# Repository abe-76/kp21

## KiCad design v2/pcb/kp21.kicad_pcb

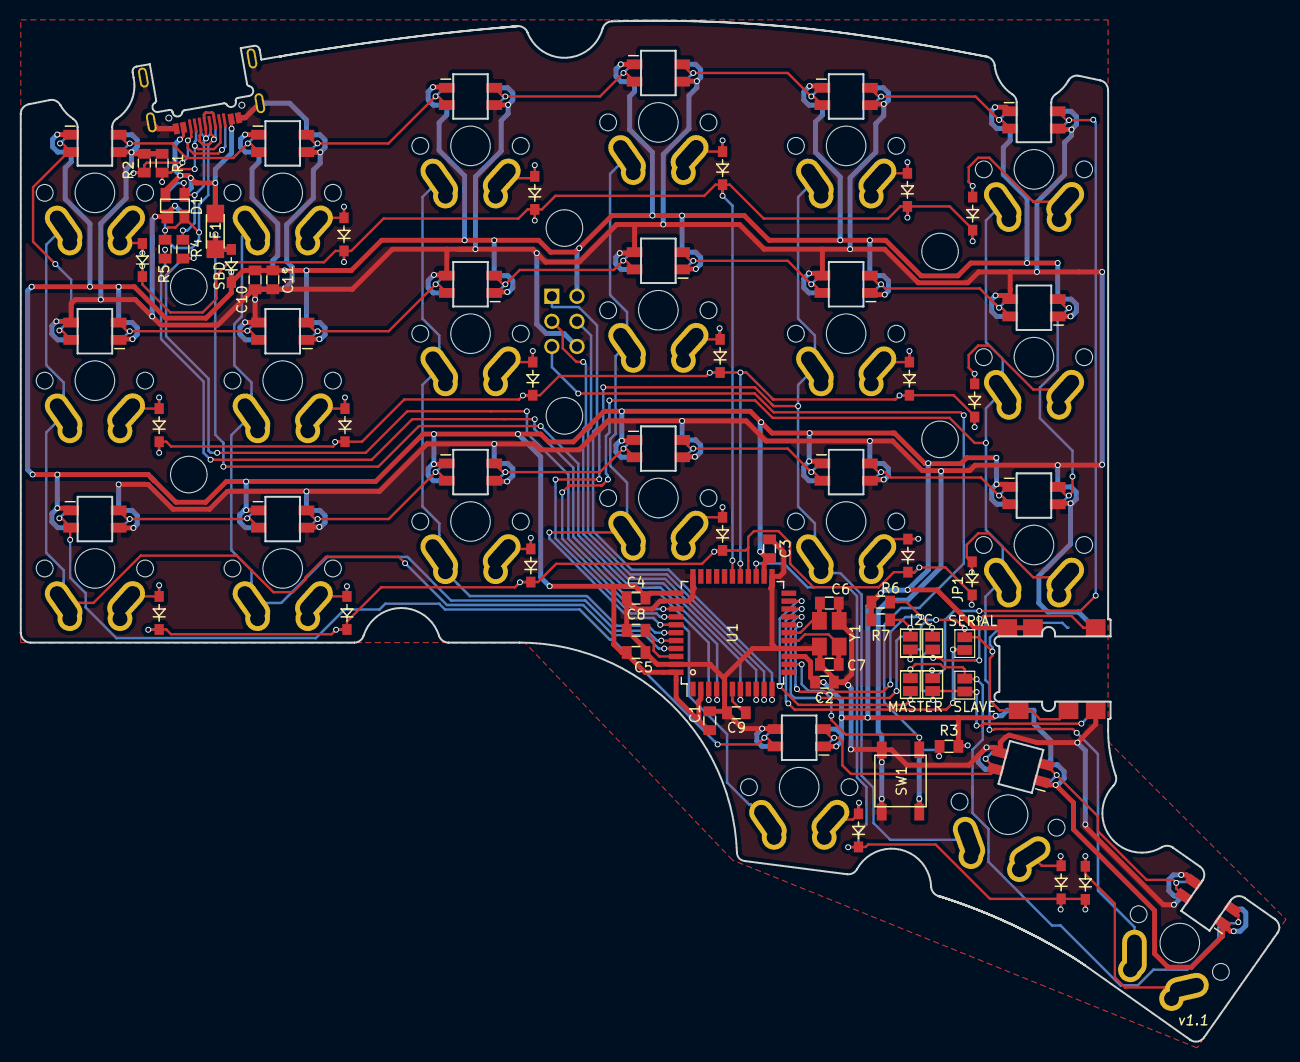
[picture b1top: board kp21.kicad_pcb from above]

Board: 2 copper layers, 127.3 x 103.3 mm, 96 parts (0 on the bottom side), 77 nets.

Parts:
C1, C2, C3, C4, C5, C8: 0.1u; 0805
C6, C7: 22p; 0805
C9: 1u; 0805
C10: 10u; 0805_rev
C11: 0.1u; 0805_rev
D1: PRTR5V0U2X; SOT-143_rev
D2: SBD; SOD-123_rev
D3, D4, D5, D6, D7, D8, D9, D10, D11, D12, D13, D14, D15, D16, D17, D18, D19, D20, D21, D22, D23: D; SOD-123_rev
F1: Polyfuse_Small; 1206_rev
J1: AVR-ISP-6
J2: 3.5mm_sj-43504_smt_tr; sj-43504
JP1, JP2, JP3, JP4, JP5, JP6: Jumper_NO_Small; SolderJumper-2_P1.3mm_Open_Pad1.0x1.5mm_rev
P1: USB_TYPE-C-31-M-14; TYPE_C_31_M_14
R1, R2: 5.1k; 0805_rev
R3: 10k; 0805_rev
R4, R5: 22; 0805_rev
R6, R7: 4.7k; 0805
SW1: SW_Push; Switch_SMD
SW2, SW3, SW4, SW5, SW6, SW7, SW8, SW9, SW10, SW11, SW12, SW13, SW14, SW15, SW16, SW17, SW18, SW19, SW20, SW21, SW22: SW_Push; SW_MX_ALPS_1u
U1: ATmega32U4; TQFP_44_pitch0.8mm
U2, U3, U4, U5, U6, U7, U8, U9, U10, U11, U12, U13, U14, U15, U16, U17, U18, U19, U20, U21, U22: SK6812mini; SK6812MINI_rev
Y1: Crystal_GND24; SMD_3225_4p

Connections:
/LED_IN: JP4.1, JP6.2, U22.3
/RESET: J1.5, R3.2, SW1.2, U1.13
/SCL: JP1.1, R6.2, U1.18
/SDA: JP2.1, R7.2, U1.19
/VBUS: D2.2, F1.1, U1.7
D+: R5.2, U1.4
D-: R4.2, U1.3
EXTRA: JP5.1, U19.1
GND: C1.2, C2.2, C3.2, C4.2, C5.2, C6.2, C7.2, C8.2, C9.2, C10.2, C11.2, D1.1, J1.6, J2.1, P1.1, P1.12, P1.13, R1.2, R2.2, SW1.1, U1.5, U1.15, U1.23, U1.33, U1.35, U1.43, U2.2, U3.2, U4.2, U5.2, U6.2, U7.2, U8.2, U9.2, U10.2, U11.2, U12.2, U13.2, U14.2, U15.2, U16.2, U17.2, U18.2, U19.2, U20.2, U21.2, U22.2, Y1.2, Y1.4
LED: JP6.1, U1.21
MISO: J1.1, U1.11
MOSI: J1.4, U1.10
unnamed: C6.1, U1.17, Y1.1
unnamed: C7.1, U1.16, Y1.3
unnamed: C8.1, U1.42
unnamed: C9.1, U1.6
unnamed: D1.2, P1.6, P1.8, R5.1
unnamed: D1.3, P1.5, P1.7, R4.1
unnamed: D1.4, F1.2, P1.2, P1.11
unnamed: D3.2, SW2.2
unnamed: D4.2, SW3.2
unnamed: D5.2, SW4.2
unnamed: D6.2, SW5.2
unnamed: D7.2, SW6.2
unnamed: D8.2, SW7.2
unnamed: D9.2, SW8.2
unnamed: D10.2, SW9.2
unnamed: D11.2, SW10.2
unnamed: D12.2, SW11.2
unnamed: D13.2, SW12.2
unnamed: D14.2, SW13.2
unnamed: D15.2, SW14.2
unnamed: D16.2, SW15.2
unnamed: D17.2, SW16.2
unnamed: D18.2, SW17.2
unnamed: D19.2, SW18.2
unnamed: D20.2, SW19.2
unnamed: D21.2, SW20.2
unnamed: D22.2, SW21.2
unnamed: D23.2, SW22.2
unnamed: J2.3, J2.6, JP2.2, JP3.2
unnamed: J2.4, JP1.2, JP4.2, JP5.2
unnamed: P1.4, R1.1
unnamed: P1.10, R2.1
unnamed: U2.1, U5.3
unnamed: U2.3, U3.1
unnamed: U3.3, U6.1
unnamed: U4.1, U7.3
unnamed: U5.1, U8.3
unnamed: U6.3, U9.1
unnamed: U10.1, U13.3
unnamed: U7.1, U10.3
unnamed: U11.1, U15.3
unnamed: U8.1, U11.3
unnamed: U9.3, U12.1
unnamed: U12.3, U16.1
unnamed: U13.1, U17.3
unnamed: U4.3, U14.1
unnamed: U14.3, U18.1
unnamed: U15.1, U19.3
unnamed: U16.3, U20.1
unnamed: U17.1, U21.3
unnamed: U18.3, U22.1
unnamed: U20.3, U21.1
SCK: J1.3, U1.9
VCC: C1.1, C2.1, C3.1, C4.1, C5.1, C10.1, C11.1, D2.1, J1.2, J2.2, J2.5, R3.1, R6.1, R7.1, U1.2, U1.14, U1.24, U1.34, U1.44, U2.4, U3.4, U4.4, U5.4, U6.4, U7.4, U8.4, U9.4, U10.4, U11.4, U12.4, U13.4, U14.4, U15.4, U16.4, U17.4, U18.4, U19.4, U20.4, U21.4, U22.4
col0: SW2.1, SW3.1, SW4.1, U1.41
col1: SW5.1, SW6.1, SW7.1, U1.40
col2: SW8.1, SW9.1, SW10.1, U1.39
col3: SW11.1, SW12.1, SW13.1, SW14.1, U1.38
col4: SW15.1, SW16.1, SW17.1, SW18.1, U1.37
col5: SW19.1, SW20.1, SW21.1, SW22.1, U1.36
data: JP3.1, U1.20
row0: D3.1, D6.1, D9.1, D12.1, D16.1, D20.1, U1.28
row1: D4.1, D7.1, D10.1, D13.1, D17.1, D21.1, U1.27
row2: D5.1, D8.1, D11.1, D14.1, D18.1, D22.1, U1.26
row3: D15.1, D19.1, D23.1, U1.25

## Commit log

2019-04-08 hole size
    hole size update
2019-04-20 update_case_master
2020-12-07 change dir
    change dir
2021-03-10 edit_drawing
